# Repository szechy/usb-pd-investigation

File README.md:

USB PD board
=======

Work in progress

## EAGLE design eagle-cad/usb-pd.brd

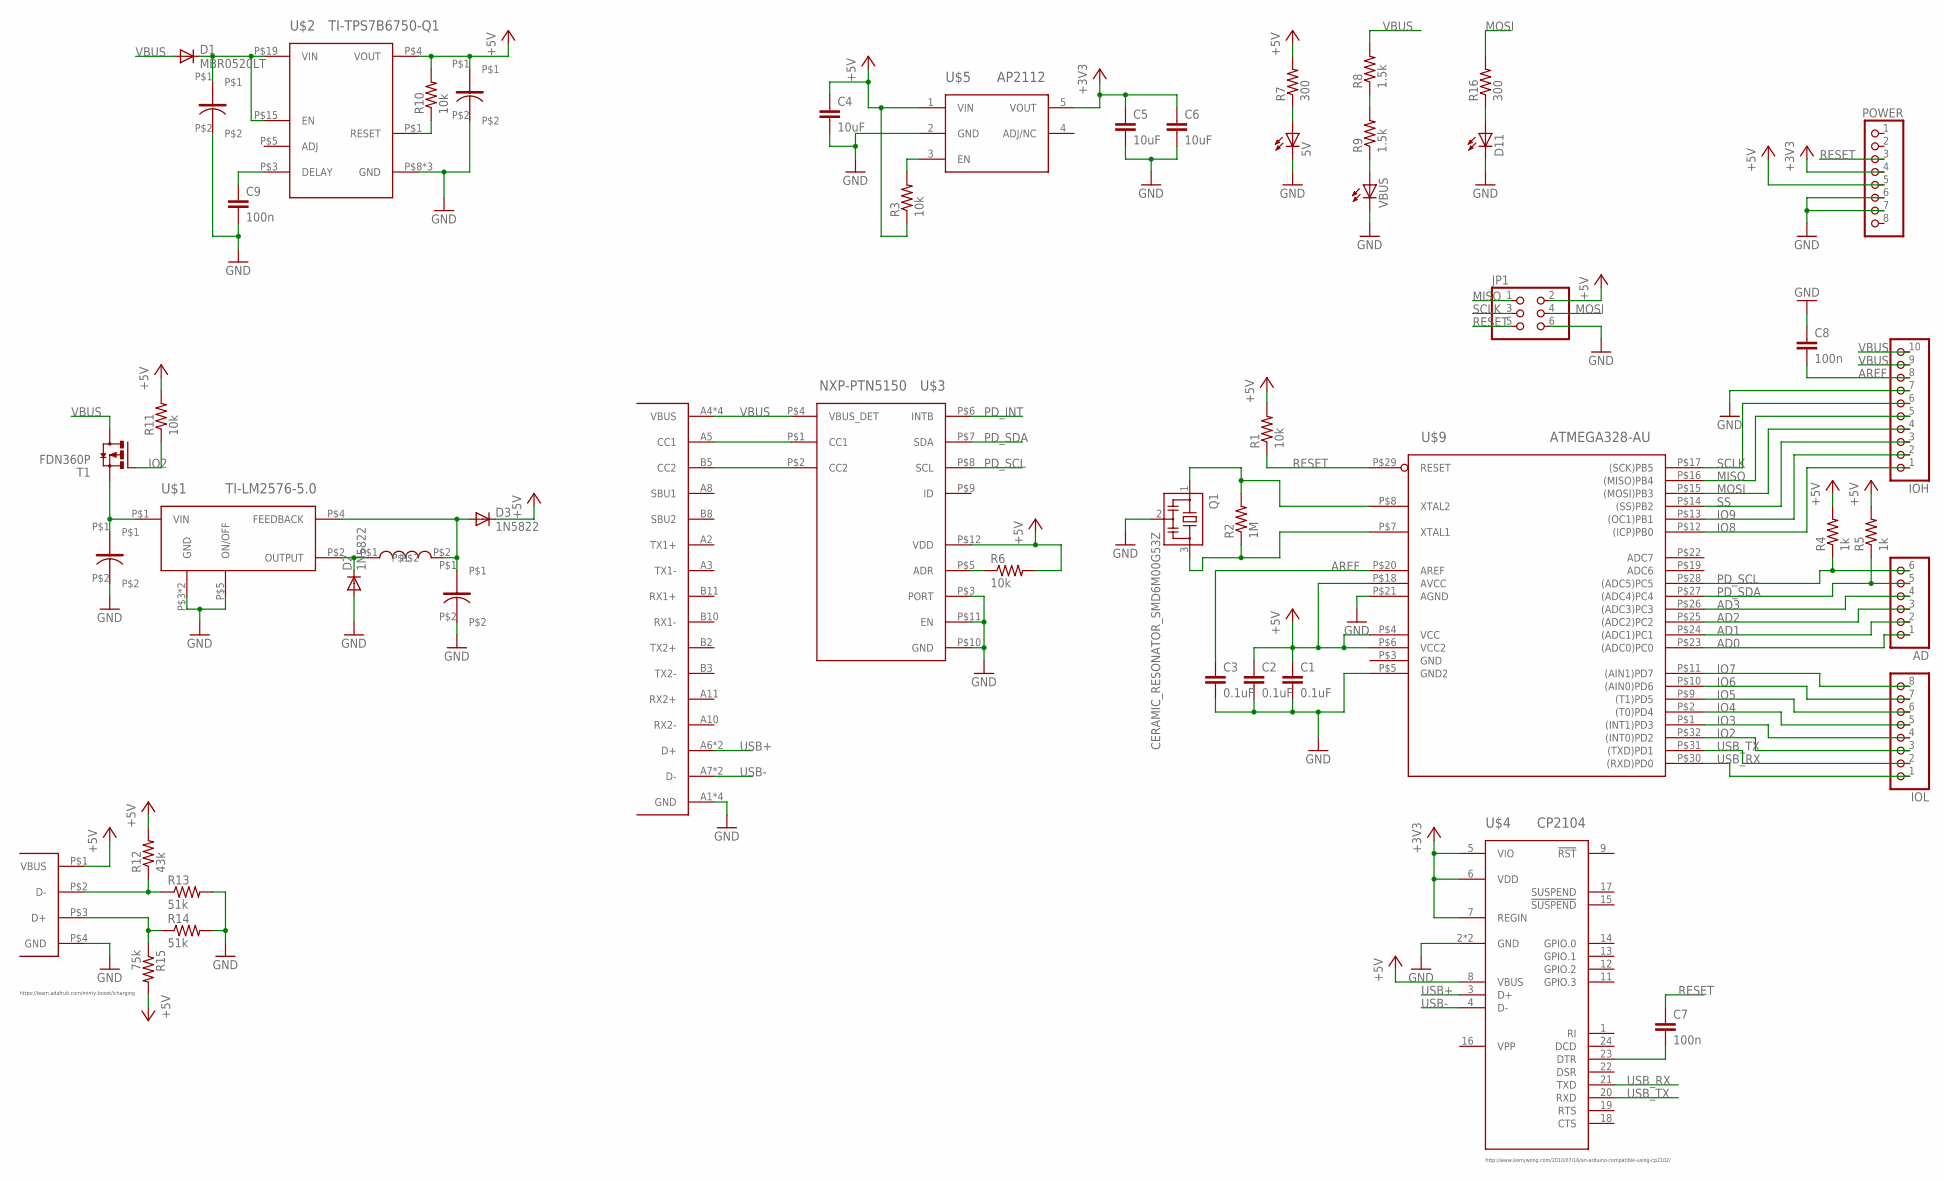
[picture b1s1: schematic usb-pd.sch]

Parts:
5V: LEDCHIPLED_0603; CHIPLED_0603
AD: PINHD-1X6; 1X06
C1, C2, C3: 0.1uF; C0402
C4, C5, C6: 10uF; C0805
C7, C8: 100n; C0402
C9: 100n; C0603
C10: UWT1V101MCL1GS
C11: AVE108M10G24T-F; AVE108M10G
C12: WURTH-865080543009-47uF; WURTH-865090543005
C13: WURTH-865090543005-22uF; WURTH-865090543005
D1: MBR0520LT; SOD123
D2, D3: 1N5822; DO201-15
D11: LEDCHIPLED_0603; CHIPLED_0603
IOH: PINHD-1X10; 1X10
IOL: PINHD-1X8; 1X08
J$1: TYPE-C-12401548E4; AMPHENOL-TYPE-C-12401548E4
J$2: UE27AC54100
JP1: PINHD-2X3; 2X03
POWER: PINHD-1X8; 1X08
Q1: CERAMIC_RESONATOR_SMD6M00G53Z; CERAMIC_RESONATOR_SMD
R1, R3, R6, R11: 10k; R0402
R2: 1M; R0402
R4, R5: 1k; R0402
R7, R16: 300; R0402
R8, R9: 1.5k; R0402
R10: 10k; R0805
R12: 43k; R0402
R13, R14: 51k; R0402
R15: 75k; R0402
T1: FDN360P; SUPER-SOT3
U$1: TI-LM2576-5.0; TO-263
U$2: TI-TPS7B6750-Q1; HTSSOP-20
U$3: NXP-PTN5150; X2QFN12
U$4: CP2104; QFN24_4X4
U$5: AP2112; SOT23-5L
U$7: WEURTH-784771101; 1260
U$9: ATMEGA328-AU; 32-TQFP
VBUS: LEDCHIPLED_0603; CHIPLED_0603

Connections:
+3V3: C5.1, C6.1, POWER.4, U$4.5 (VIO), U$4.6 (VDD), U$4.7 (REGIN), U$5.5 (VOUT)
+5V: C1.1, C2.1, C4.1, C13.P$1, D3.C, J$2.P$1 (VBUS), JP1.2, POWER.5, R1.2, R3.1, R4.2, R5.2, R6.2, R7.2, R10.2, R11.2, R12.2, R15.2, U$2.P$4 (VOUT), U$3.P$12 (VDD), U$4.8 (VBUS), U$5.1 (VIN), U$9.P$4 (VCC), U$9.P$6 (VCC2), U$9.P$18 (AVCC)
AD0: AD.1, U$9.P$23 ((ADC0)PC0)
AD1: AD.2, U$9.P$24 ((ADC1)PC1)
AD2: AD.3, U$9.P$25 ((ADC2)PC2)
AD3: AD.4, U$9.P$26 ((ADC3)PC3)
AREF: C3.1, C8.2, IOH.8, U$9.P$20 (AREF)
GND: 5V.C, C1.2, C2.2, C3.2, C4.2, C5.2, C6.2, C8.1, C9.2, C10.P$2, C11.P$2, C12.P$2, C13.P$2, D2.A, D11.C, IOH.7, J$1.A1 (GND), J$1.A12 (GND), J$1.B1 (GND), J$1.B12 (GND), J$2.P$4 (GND), JP1.6, POWER.6, POWER.7, Q1.2, R13.2, R14.2, U$1.P$3 (GND), U$1.P$5 (ON/OFF), U$1.P$6 (GND), U$2.P$8 (GND), U$2.P$13 (GND), U$2.P$21 (GND), U$3.P$3 (PORT), U$3.P$10 (GND), U$3.P$11 (EN), U$4.2 (GND), U$4.25 (GND), U$5.2 (GND), U$9.P$5 (GND2), U$9.P$21 (AGND), VBUS.C
IO2: IOL.3, R11.1, T1.1 (G), U$9.P$32 ((INT0)PD2)
IO3: IOL.4, U$9.P$1 ((INT1)PD3)
IO4: IOL.5, U$9.P$2 ((T0)PD4)
IO5: IOL.6, U$9.P$9 ((T1)PD5)
IO6: IOL.7, U$9.P$10 ((AIN0)PD6)
IO7: IOL.8, U$9.P$11 ((AIN1)PD7)
IO8: IOH.1, U$9.P$12 ((ICP)PB0)
IO9: IOH.2, U$9.P$13 ((OC1)PB1)
MISO: IOH.5, JP1.1, U$9.P$16 ((MISO)PB4)
MOSI: IOH.4, JP1.4, R16.2, U$9.P$15 ((MOSI)PB3)
unnamed: C10.P$1, T1.2 (S), U$1.P$1 (VIN)
unnamed: Q1.3, R2.1, U$9.P$7 (XTAL1)
unnamed: Q1.1, R2.2, U$9.P$8 (XTAL2)
unnamed: C7.2, U$4.23 (DTR)
unnamed: J$1.A5 (CC1), U$3.P$1 (CC1)
unnamed: J$1.B5 (CC2), U$3.P$2 (CC2)
unnamed: R3.2, U$5.3 (EN)
unnamed: R6.1, U$3.P$5 (ADR)
unnamed: D2.C, U$1.P$2 (OUTPUT), U$7.P$1
unnamed: 5V.A, R7.1
unnamed: R9.1, VBUS.A
unnamed: R8.1, R9.2
unnamed: R10.1, U$2.P$1 (RESET)
unnamed: C9.1, U$2.P$3 (DELAY)
unnamed: C11.P$1, D3.A, U$1.P$4 (FEEDBACK), U$7.P$2
unnamed: D11.A, R16.1
unnamed: J$2.P$2 (D-), R12.1, R13.1
unnamed: J$2.P$3 (D+), R14.1, R15.1
unnamed: C12.P$1, D1.C, U$2.P$15 (EN), U$2.P$19 (VIN)
PD_INT: U$3.P$6 (INTB)
PD_SCL: AD.6, R4.1, U$3.P$8 (SCL), U$9.P$28 ((ADC5)PC5)
PD_SDA: AD.5, R5.1, U$3.P$7 (SDA), U$9.P$27 ((ADC4)PC4)
RESET: C7.1, JP1.5, POWER.3, R1.1, U$9.P$29 (RESET)
SCLK: IOH.6, JP1.3, U$9.P$17 ((SCK)PB5)
SS: IOH.3, U$9.P$14 ((SS)PB2)
USB+: J$1.A6 (D+), J$1.B6 (D+), U$4.3 (D+)
USB-: J$1.A7 (D-), J$1.B7 (D-), U$4.4 (D-)
USB_RX: IOL.1, U$4.21 (TXD), U$9.P$30 ((RXD)PD0)
USB_TX: IOL.2, U$4.20 (RXD), U$9.P$31 ((TXD)PD1)
VBUS: D1.A, IOH.9, IOH.10, J$1.A4 (VBUS), J$1.A9 (VBUS), J$1.B4 (VBUS), J$1.B9 (VBUS), R8.2, T1.3 (D), U$3.P$4 (VBUS_DET)

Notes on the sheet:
http://www.kerrywong.com/2010/07/16/an-arduino-compatible-using-cp2102/
https://learn.adafruit.com/minty-boost/icharging

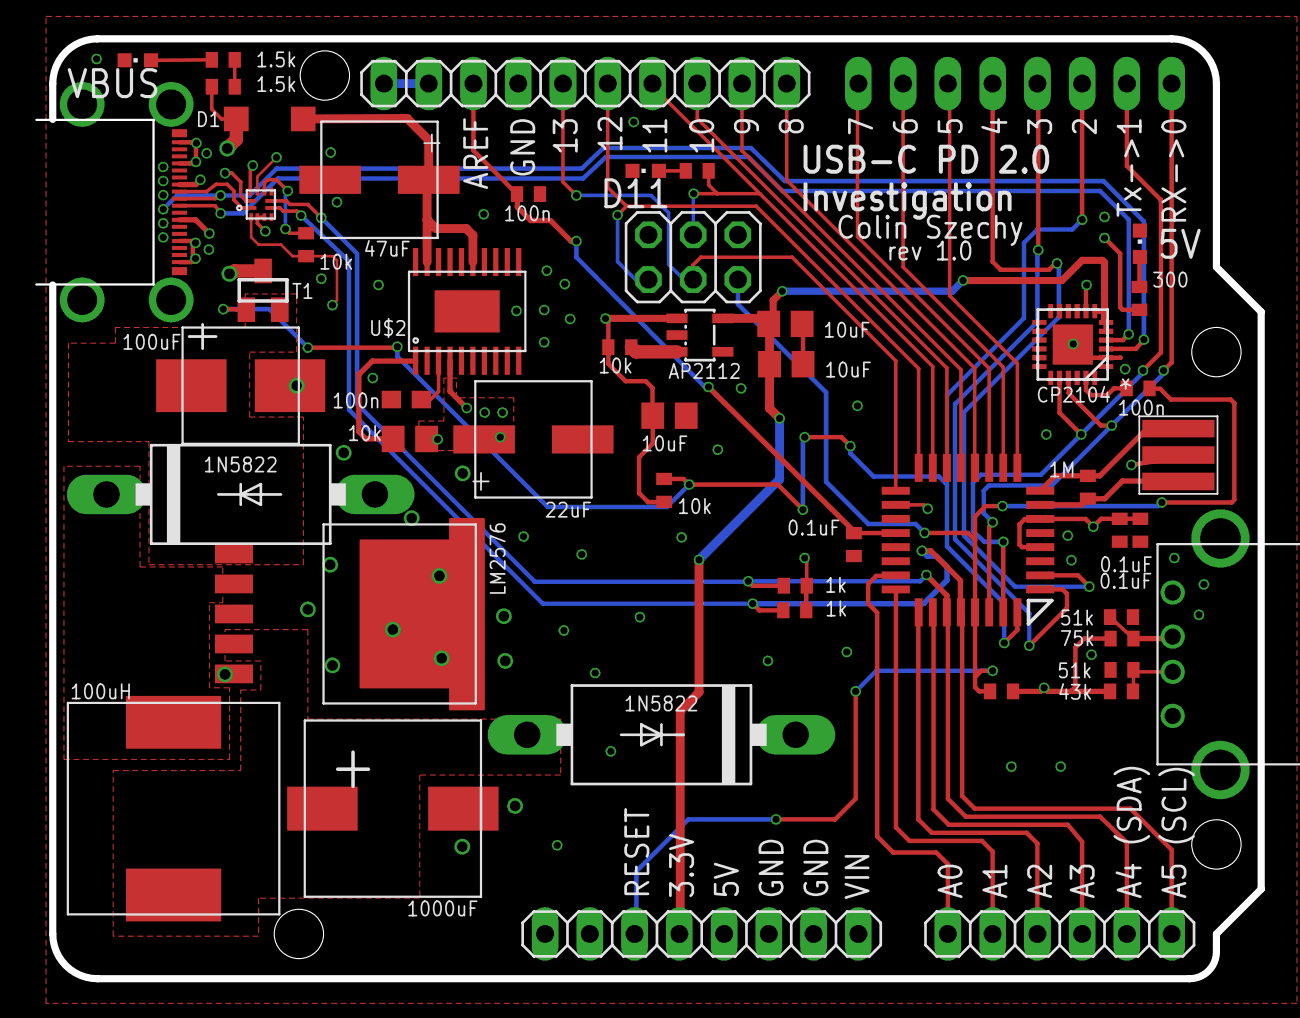
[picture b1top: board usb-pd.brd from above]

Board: 4 copper layers, 69.4 x 53.3 mm, 51 parts (1 on the bottom side), 47 nets.

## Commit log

2016-12-22 Added five main/important/complicated parts to library
2016-12-22 Started EAGLE schematic with copying ATMEga328 implementation from Arduino Uno, adding CP2104 implementation, 3v3 LDO implementation from MHacks Hacker Boards
2016-12-22 Filled out PTN5150, arranged board like an Uno rev3
2016-12-23 Added 5V buck implementation (need power FET to control it)
2016-12-23 Added a n-channel power MOSFET to serve as controlling power FET for 5V buck. Definitely needs review
2016-12-23 switched to p-channel because I'm dumb
2016-12-23 Started researching proper capacitors, modified parts to have name and value on schematic
2016-12-23 Finished placement, started routing
2016-12-24 Entire-board-routed, rev-1. This is going to need a lot of revisions.
2016-12-24 Added stitching vias and played with ground planes
2016-12-24 Pushed DRC down to only 17 errors (from 550)
2016-12-24 Fix disconnected ground plane
2016-12-25 Added new USB-C port, going to look at four-layer boards to get better Osh Park hole tolerances and ton of space for power planes
2016-12-25 Minor changes
2016-12-30 Went to a 4-layer board design with a stackup of signal, GND, VCC, signal
2016-12-30 Added new TypeC connector that has vias instead of slots - Osh Park can't do slots that small
2017-01-02 Fixed notch by USB-C port as per OSH Park support ticket around slots
